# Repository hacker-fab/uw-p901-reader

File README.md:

# P901 Interface
We use the MKS 901P loadlock vacuum transducer to read vacuum pressures in our chambers. Unfortunately, it doesn't come with a display.

This codebase contains several folders:
- **901p-board-v2** - custom ESP32-based board with display.
- **901p-board-v2-code** - code for the above board, written for Arduino.
- **901p-serial** - Python library for interfacing with the thing over RS232 serial.
- **901p-serial-io-board** - breakout board to make it easier to get power and serial connections.

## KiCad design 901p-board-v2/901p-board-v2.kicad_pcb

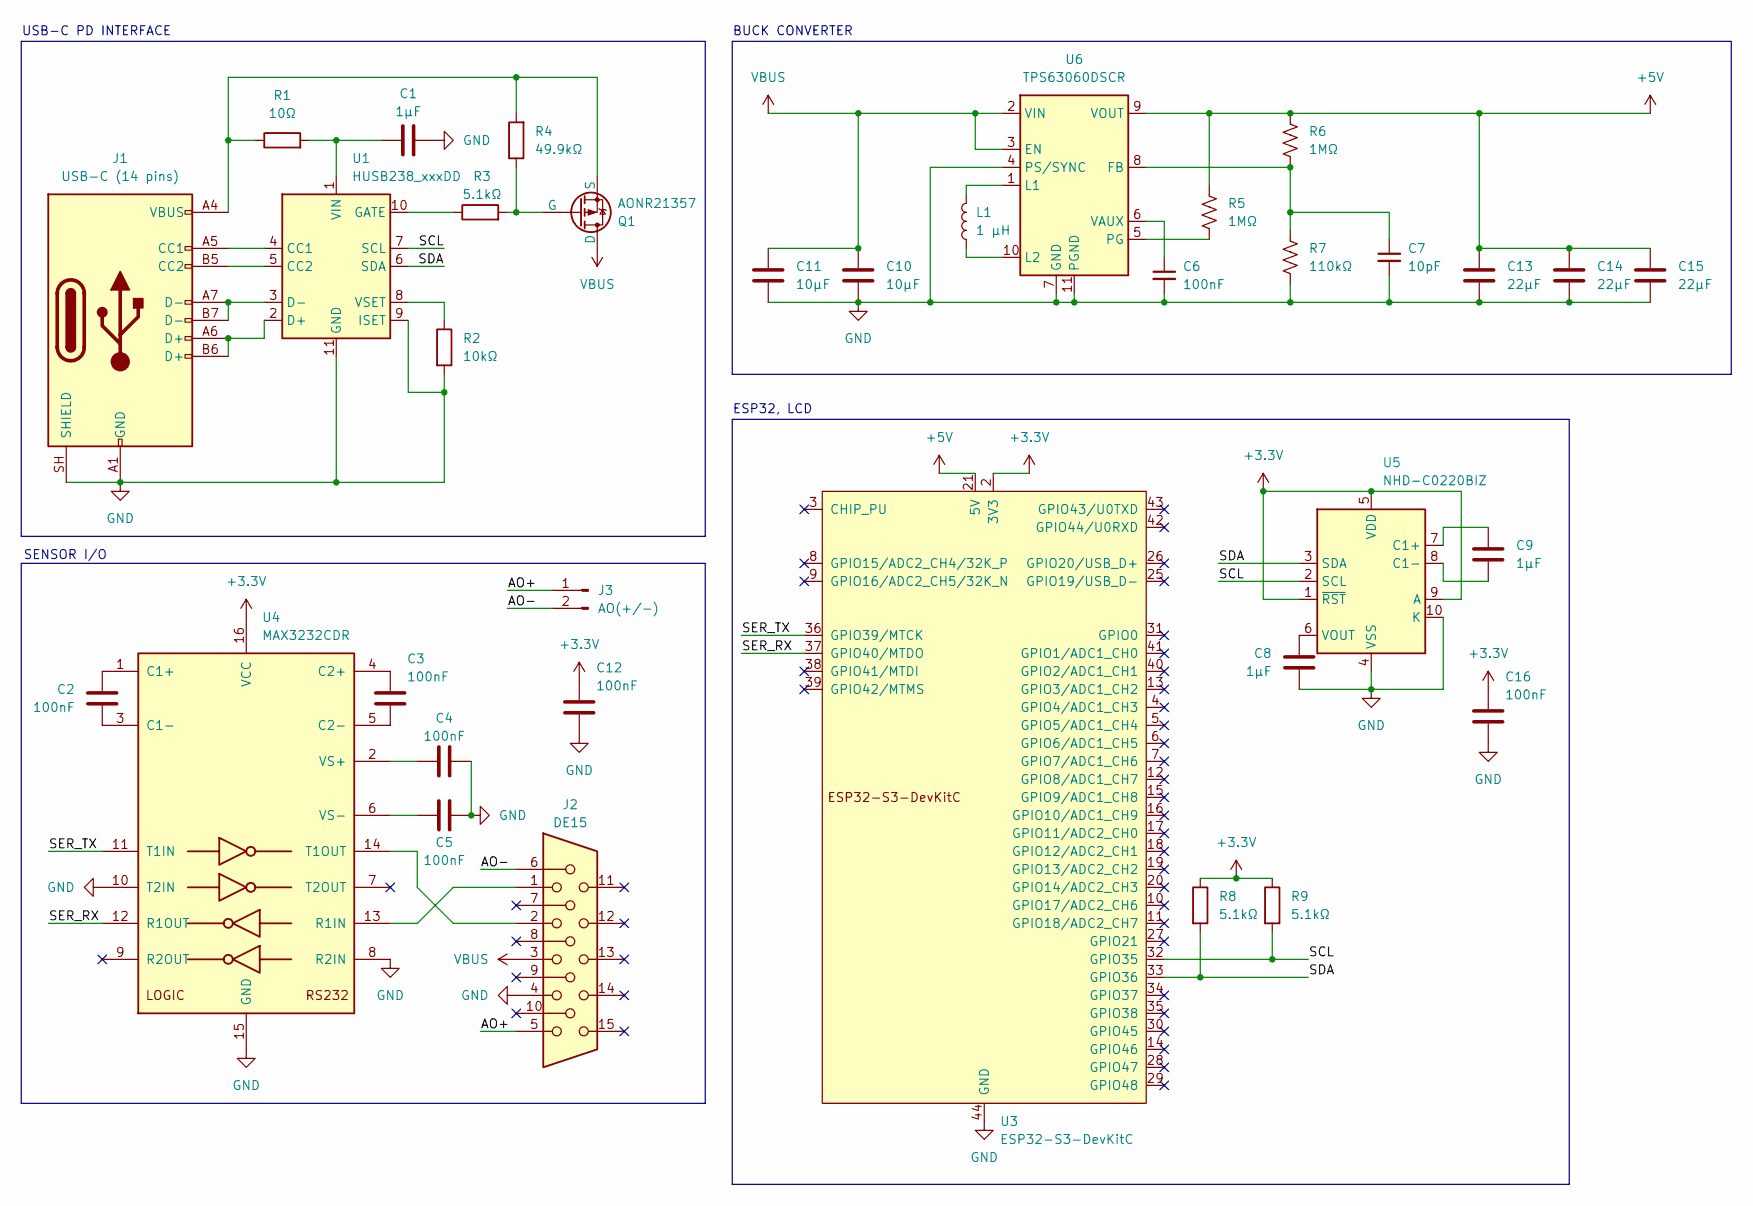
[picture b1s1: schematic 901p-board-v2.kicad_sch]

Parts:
C1, C8, C9: 1µF; C_0805_2012Metric_Pad1.18x1.45mm_HandSolder; Digikey 1276-6470-1-ND
C2, C3, C4, C5, C6, C12, C16: 100nF; C_0805_2012Metric_Pad1.18x1.45mm_HandSolder; Digikey 1276-1003-1-ND
C7: 10pF; C_0805_2012Metric_Pad1.18x1.45mm_HandSolder; Digikey 1276-2561-1-ND
C10, C11: 10µF; C_0805_2012Metric_Pad1.18x1.45mm_HandSolder; Digikey 1276-6457-1-ND
C13, C14, C15: 22µF; C_0805_2012Metric_Pad1.18x1.45mm_HandSolder; Digikey 1276-6501-1-ND
J1: USB-C (14 pins); UJ20-C-H-G-SMT-2A-P16-TR; Digikey 2223-UJ20-C-H-G-SMT-2A-P16-TRCT-ND
J2: DE15; AMPHENOL_10090926-P154XLF; Digikey 10090926-P154XLF
J3: AO(+/-); PinHeader_1x02_P2.54mm_Vertical
L1: 1 μH; L_1210_3225Metric_Pad1.42x2.65mm_HandSolder; Digikey 490-18403-1-ND
Q1: AONR21357; PPAK3x3; Digikey 785-AONR21357CT-ND
R1: 10Ω; R_0805_2012Metric_Pad1.20x1.40mm_HandSolder; Digikey 311-10.0CRCT-ND
R2: 10kΩ; R_0805_2012Metric_Pad1.20x1.40mm_HandSolder; Digikey 311-10.0KCRCT-ND
R3, R8, R9: 5.1kΩ; R_0805_2012Metric_Pad1.20x1.40mm_HandSolder; Digikey 311-5.1KARCT-ND
R4: 49.9kΩ; R_0805_2012Metric_Pad1.20x1.40mm_HandSolder; Digikey 311-49.9KCRCT-ND
R5, R6: 1MΩ; R_0805_2012Metric_Pad1.20x1.40mm_HandSolder; Digikey 311-1.00MCRCT-ND
R7: 110kΩ; R_0805_2012Metric_Pad1.20x1.40mm_HandSolder; Digikey 311-110KARCT-ND
U1: HUSB238_xxxDD; WDFN-10-1EP_3x3mm_P0.5mm_EP1.8x2.5mm
U3: ESP32-S3-DevKitC
U4: MAX3232CDR; D16; Digikey 296-13094-1-ND
U5: NHD-C0220BIZ; NHD-C0220BiZ; Digikey NHD-C0220BIZ-FSW-FBW-3V3M-ND
U6: TPS63060DSCR; Texas_S-PWSON-N10_ThermalVias; Digikey 296-30204-1-ND

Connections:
+3.3V: C12.1, C16.1, R8.1, R9.1, U3.1 (3V3), U3.2 (3V3), U4.16 (VCC), U5.1 (~RST), U5.5 (VDD), U5.9 (A)
+5V: C13.1, C14.1, C15.1, R5.1, R6.1, U3.21 (5V), U6.9 (VOUT)
/AO+: J2.5, J3.1
/AO-: J2.6, J3.2
/SCL: R9.2, U1.7 (SCL), U3.32 (GPIO35), U5.2 (SCL)
/SDA: R8.2, U1.6 (SDA), U3.33 (GPIO36), U5.3 (SDA)
/SER_RX: U3.37 (GPIO40/MTDO), U4.12 (R1OUT)
/SER_TX: U3.36 (GPIO39/MTCK), U4.11 (T1IN)
GND: C1.2, C4.2, C5.2, C6.2, C7.2, C8.2, C10.2, C11.2, C12.2, C13.2, C14.2, C15.2, C16.2, J1.A1 (GND), J1.A12 (GND), J1.B1 (GND), J1.B12 (GND), J1.SH (SHIELD), J2.4, R2.2, R7.2, U1.9 (ISET), U1.11 (GND), U3.22 (GND), U3.23 (GND), U3.24 (GND), U3.44 (GND), U4.8 (R2IN), U4.10 (T2IN), U4.15 (GND), U5.4 (VSS), U5.10 (K), U6.4 (PS/SYNC), U6.7 (GND), U6.11 (PGND)
unnamed: J1.A5 (CC1), U1.4 (CC1)
unnamed: J1.B5 (CC2), U1.5 (CC2)
unnamed: Q1.2 (G), R3.2, R4.1
unnamed: J1.A4 (VBUS), J1.A9 (VBUS), J1.B4 (VBUS), J1.B9 (VBUS), Q1.3 (S), R1.1, R4.2
unnamed: J1.A6 (D+), J1.B6 (D+), U1.2 (D+)
unnamed: J1.A7 (D-), J1.B7 (D-), U1.3 (D-)
unnamed: R3.1, U1.10 (GATE)
unnamed: C1.1, R1.2, U1.1 (VIN)
unnamed: R2.1, U1.8 (VSET)
unnamed: C2.1, U4.1 (C1+)
unnamed: C2.2, U4.3 (C1-)
unnamed: C3.1, U4.4 (C2+)
unnamed: C3.2, U4.5 (C2-)
unnamed: J2.1, U4.13 (R1IN)
unnamed: J2.2, U4.14 (T1OUT)
unnamed: C4.1, U4.2 (VS+)
unnamed: C5.1, U4.6 (VS-)
unnamed: C9.1, U5.7 (C1+)
unnamed: C9.2, U5.8 (C1-)
unnamed: C8.1, U5.6 (VOUT)
unnamed: C7.1, R6.2, R7.1, U6.8 (FB)
unnamed: L1.1, U6.1 (L1)
unnamed: L1.2, U6.10 (L2)
unnamed: R5.2, U6.5 (PG)
unnamed: C6.1, U6.6 (VAUX)
VBUS: C10.1, C11.1, J2.3, Q1.1 (D), U6.2 (VIN), U6.3 (EN)

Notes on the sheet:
ESP32, LCD
USB-C PD INTERFACE
SENSOR I/O
BUCK CONVERTER

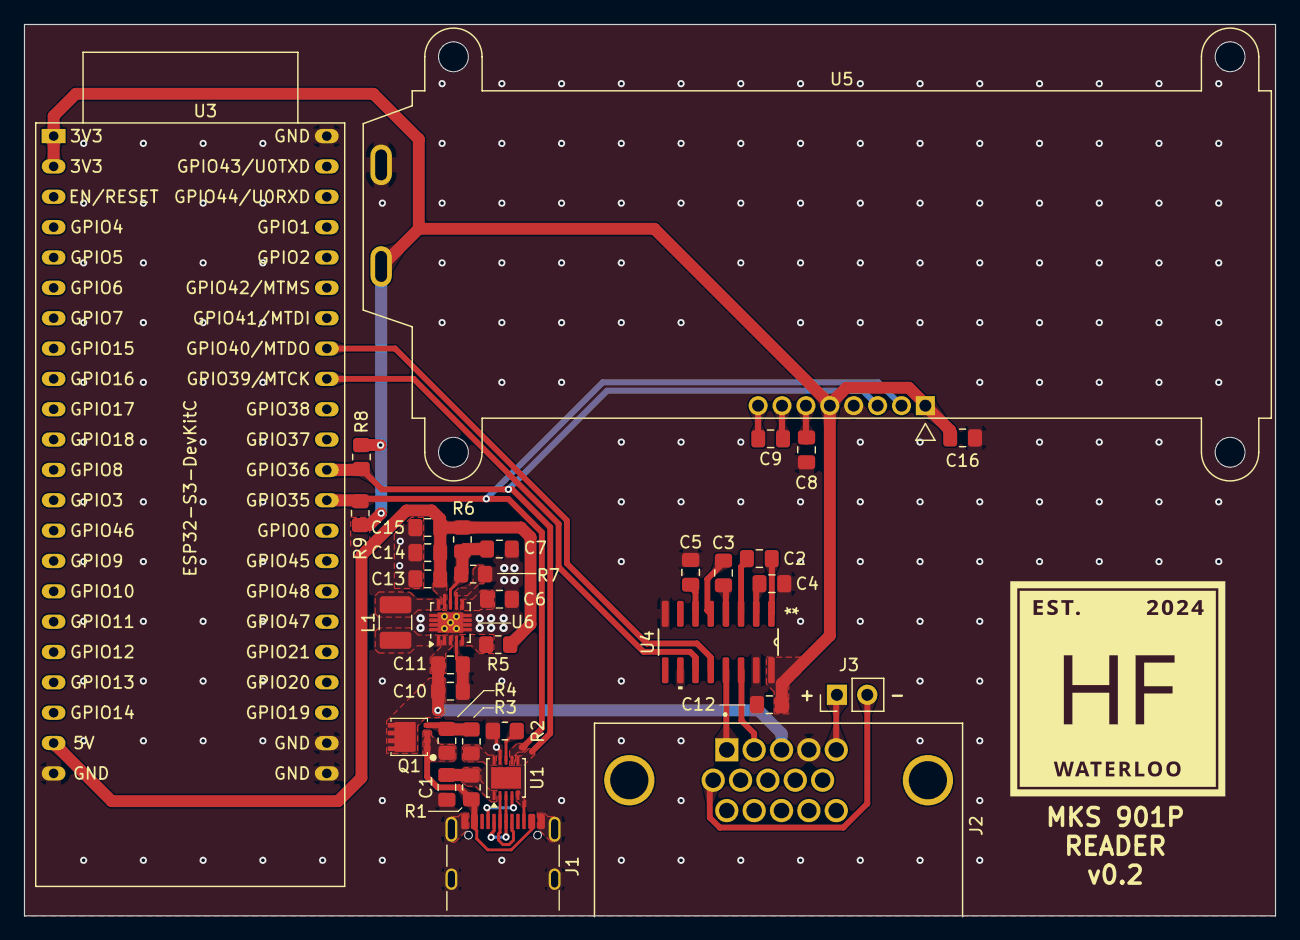
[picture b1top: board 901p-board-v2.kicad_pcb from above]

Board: 2 copper layers, 104.7 x 74.6 mm, 35 parts (0 on the bottom side), 35 nets.

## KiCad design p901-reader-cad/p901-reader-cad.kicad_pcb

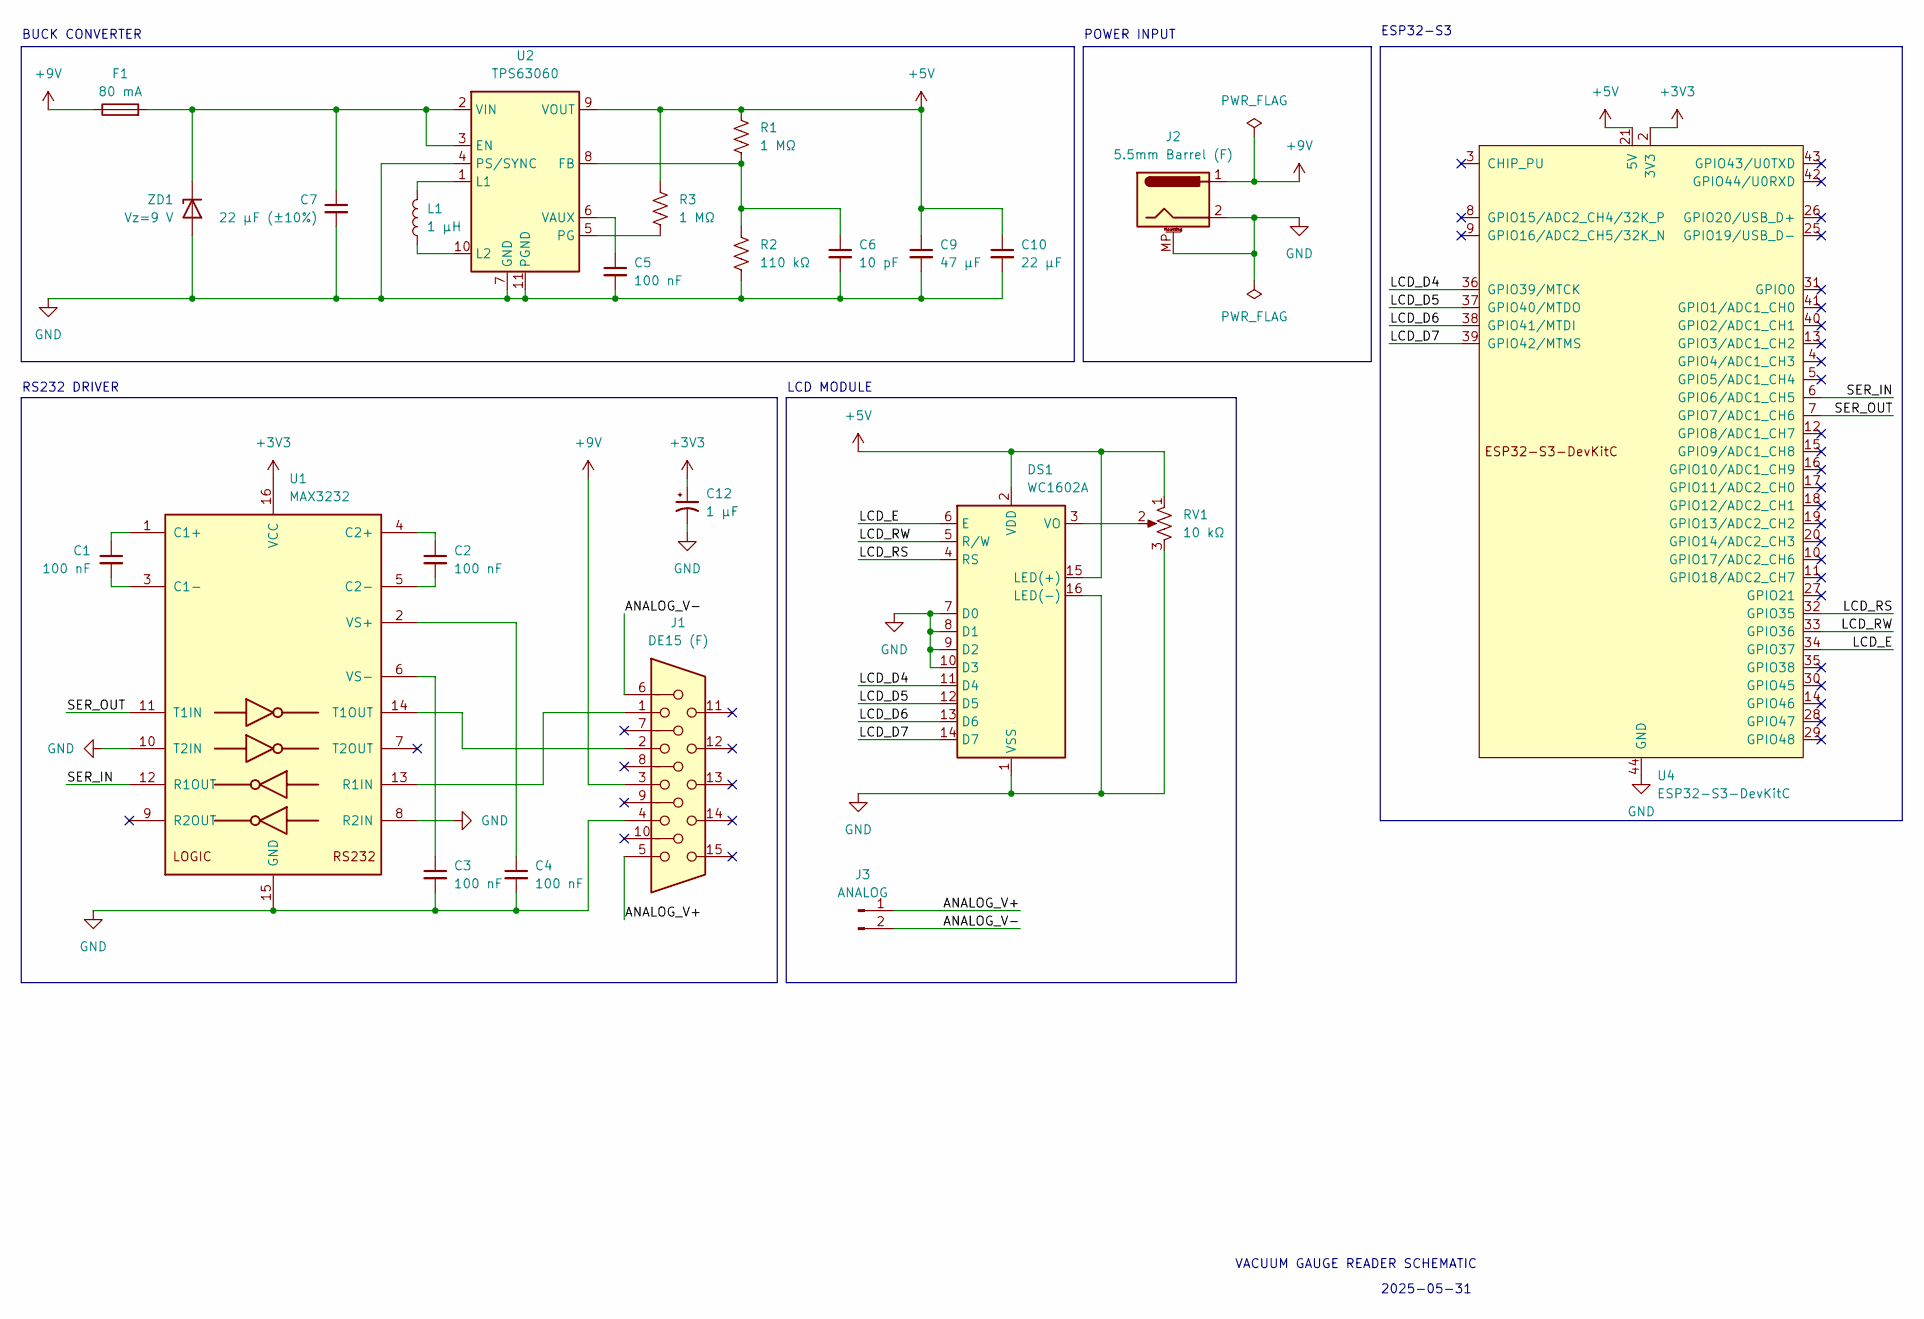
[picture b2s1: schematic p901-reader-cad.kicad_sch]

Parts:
C1, C2, C3, C4, C5: 100 nF; C_0805_2012Metric_Pad1.18x1.45mm_HandSolder; LCSC CC0805KRX7R9BB104
C6: 10 pF; C_0805_2012Metric_Pad1.18x1.45mm_HandSolder; LCSC CC0805JRNPO9BN100
C7: 22 μF (±10%); C_1206_3216Metric_Pad1.33x1.80mm_HandSolder; LCSC CL31A226KAHNNNE
C9: 47 μF; C_0805_2012Metric_Pad1.18x1.45mm_HandSolder; LCSC CL31A476MPHNNNE
C10: 22 μF; C_0805_2012Metric_Pad1.18x1.45mm_HandSolder; LCSC CL21A226MAQNNNE
C12: 1 μF; C_0805_2012Metric_Pad1.18x1.45mm_HandSolder; LCSC CL21B105KBFNNNE
DS1: WC1602A
F1: 80 mA; Fuseholder_TR5_Littelfuse_No560_No460
J1: DE15 (F); AMPHENOL_10090926-P154XLF
J2: 5.5mm Barrel (F); CUI_PJ-002B
J3: ANALOG; PinSocket_1x02_P2.54mm_Vertical
L1: 1 μH; L_1210_3225Metric_Pad1.42x2.65mm_HandSolder
R1, R3: 1 MΩ; R_0805_2012Metric_Pad1.20x1.40mm_HandSolder; LCSC 0805W8F1004T5E
R2: 110 kΩ; R_0805_2012Metric_Pad1.20x1.40mm_HandSolder; LCSC 0805W8F1103T5E
RV1: 10 kΩ; 601030_AVX
U1: MAX3232; SOIC-16W_7.5x10.3mm_P1.27mm
U2: TPS63060; Texas_S-PWSON-N10_ThermalVias; LCSC TPS63060DSCR
U4: ESP32-S3-DevKitC
ZD1: Vz=9 V; D_1812_4532Metric

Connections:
+3V3: C12.1, U1.16 (VCC), U4.1 (3V3), U4.2 (3V3)
+5V: C9.1, C10.1, DS1.2 (VDD), DS1.15 (LED(+)), R1.1, R3.1, RV1.1, U2.9 (VOUT), U4.21 (5V)
+9V: F1.1, J1.3, J2.1
/ANALOG_V+: J1.5, J3.1
/ANALOG_V-: J1.6, J3.2
/LCD_D4: DS1.11 (D4), U4.36 (GPIO39/MTCK)
/LCD_D5: DS1.12 (D5), U4.37 (GPIO40/MTDO)
/LCD_D6: DS1.13 (D6), U4.38 (GPIO41/MTDI)
/LCD_D7: DS1.14 (D7), U4.39 (GPIO42/MTMS)
/LCD_E: DS1.6 (E), U4.34 (GPIO37)
/LCD_RS: DS1.4 (RS), U4.32 (GPIO35)
/LCD_RW: DS1.5 (R/W), U4.33 (GPIO36)
/SER_IN: U1.12 (R1OUT), U4.6 (GPIO6/ADC1_CH5)
/SER_OUT: U1.11 (T1IN), U4.7 (GPIO7/ADC1_CH6)
GND: C3.2, C4.2, C5.2, C6.2, C7.2, C9.2, C10.2, C12.2, DS1.1 (VSS), DS1.7 (D0), DS1.8 (D1), DS1.9 (D2), DS1.10 (D3), DS1.16 (LED(-)), J1.4, J2.2, J2.MP (MountPin_MP), R2.2, RV1.3, U1.8 (R2IN), U1.10 (T2IN), U1.15 (GND), U2.4 (PS/SYNC), U2.7 (GND), U2.11 (PGND), U4.22 (GND), U4.23 (GND), U4.24 (GND), U4.44 (GND), ZD1.2 (A)
unnamed: DS1.3 (VO), RV1.2
unnamed: C1.1, U1.1 (C1+)
unnamed: C1.2, U1.3 (C1-)
unnamed: C2.1, U1.4 (C2+)
unnamed: C2.2, U1.5 (C2-)
unnamed: J1.1, U1.13 (R1IN)
unnamed: J1.2, U1.14 (T1OUT)
unnamed: C4.1, U1.2 (VS+)
unnamed: C3.1, U1.6 (VS-)
unnamed: C7.1, F1.2, U2.2 (VIN), U2.3 (EN), ZD1.1 (K)
unnamed: C6.1, R1.2, R2.1, U2.8 (FB)
unnamed: L1.1, U2.1 (L1)
unnamed: L1.2, U2.10 (L2)
unnamed: R3.2, U2.5 (PG)
unnamed: C5.1, U2.6 (VAUX)

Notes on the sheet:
POWER INPUT
RS232 DRIVER
BUCK CONVERTER
LCD MODULE
ESP32-S3
2025-05-31
VACUUM GAUGE READER SCHEMATIC

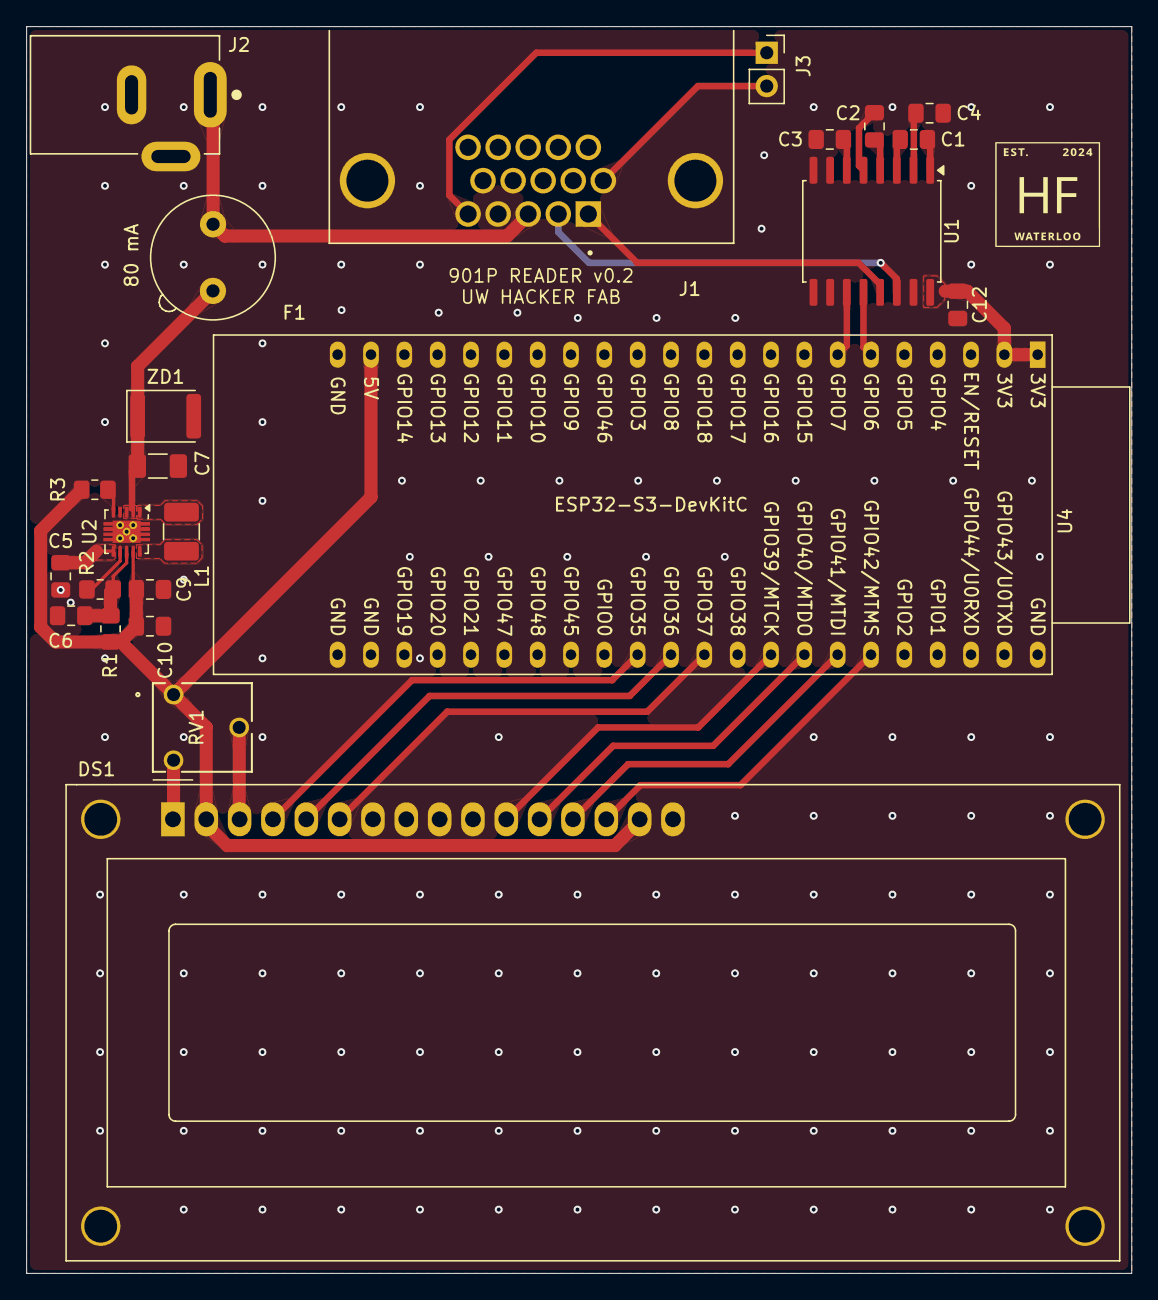
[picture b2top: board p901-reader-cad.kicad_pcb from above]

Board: 2 copper layers, 84.2 x 95.0 mm, 24 parts (0 on the bottom side), 30 nets.

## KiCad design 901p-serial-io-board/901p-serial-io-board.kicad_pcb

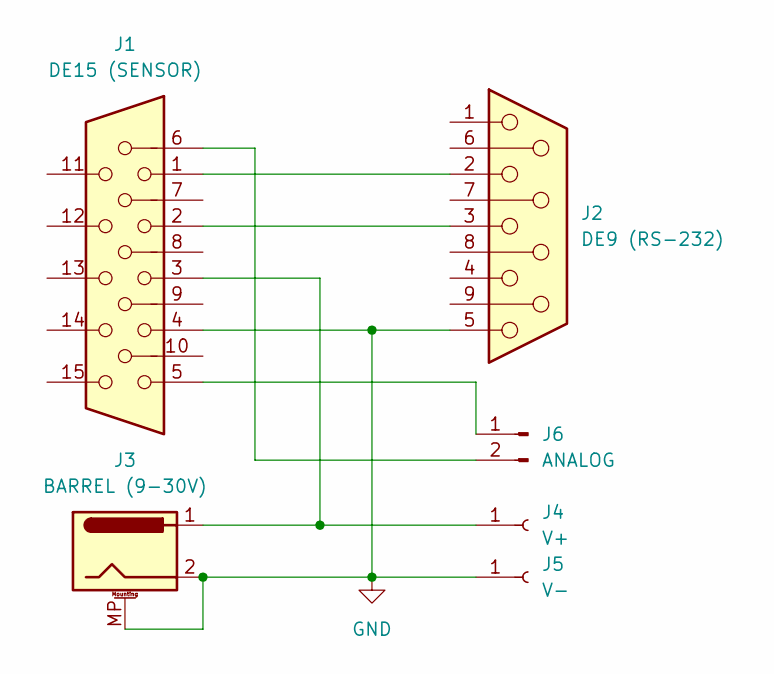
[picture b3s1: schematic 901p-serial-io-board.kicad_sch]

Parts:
J1: DE15 (SENSOR); AMPHENOL_ICD15S13E4GX00LF
J2: DE9 (RS-232); AMPHENOL_LD09S33E4GV00LF
J3: BARREL (9-30V); CUI_PJ-002B
J4: V+; CINCH_105-1102-001
J5: V-; CINCH_105-1102-001
J6: ANALOG; PinHeader_1x02_P2.54mm_Vertical

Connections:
GND: J1.4, J2.5, J3.2, J3.MP (MountPin), J5.1
unnamed: J1.1, J2.2
unnamed: J1.2, J2.3
unnamed: J1.3, J3.1, J4.1
unnamed: J1.5, J6.1
unnamed: J1.6, J6.2

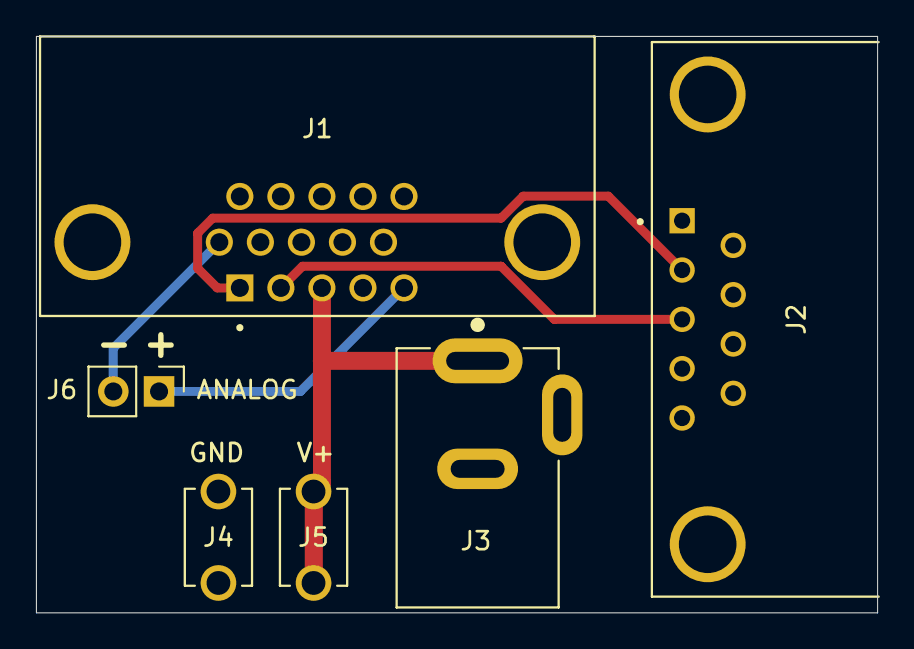
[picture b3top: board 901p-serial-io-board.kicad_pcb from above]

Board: 2 copper layers, 46.7 x 32.0 mm, 6 parts (0 on the bottom side), 6 nets.

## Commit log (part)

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2025-06-04 it's gitting time
2025-06-04 update the readme
2025-06-05 redo the PCB since it kinda sucked
2025-06-05 add via stitches, clean up random crap lying around
2025-06-05 whoops missed some vias
2025-06-05 fix the silly pinout error
2025-06-09 fixed DRC warning from mismatched footprint
2025-06-10 bump: JLC selections
2025-06-10 fix DRC again
2025-06-13 Crude Rust example that I got working on the ESP.
2026-02-10 add new code to old repo
2026-02-12 new board ooh
2026-03-19 fix board pinout, add analog headers
2026-03-19 ok final reroute for real
2026-03-19 added esp32 code for hacked reader board
2026-03-20 improve print formatting
2026-03-20 add window average for rate of change
2026-03-20 miniaturized board
2026-03-20 re-add labelling on back side
2026-04-03 update to KiCAD 10.0, reroute against official ESP footprints
2026-04-03 add stitching vias
2026-05-25 redesign power to use USB-C PD
2026-05-29 v2 board stuff
2026-06-02 finish v2 board
2026-06-03 fix stitching vias, add more zones
2026-06-03 final review i think
2026-06-04 remove this cursed history thing that keeps screwing with Git
